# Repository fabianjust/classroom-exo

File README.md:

# classroom-exo
Classroom-ready open-source educational exoskeleton for biomedical and control engineering

The classroom Exo development is guided by the manual.
The manual is designed to assist you in seamlessly transitioning from EduExoPro to Classroom Exo. Whether you're a developer, educator, or enthusiast, the detailed content in each folder aims to provide clarity and guidance.

How to Use This Manual:
Begin by reading through the manual to familiarize yourself with the upgrade process.
Depending on your area of interest or expertise, navigate to the specific folders that match your requirements—whether it's CAD, PCB design, electronics, or material lists.
Feel free to collaborate by providing feedback, raising issues, or contributing to the ongoing development of Classroom Exo. Your input is highly valued.

We prepared three lab instructions for a) Force Control, b) Muscle Activity Control, and c) PID Control for Biomedical and Control Engineering University Education. Feel free to use these documents to build your own lab for a physical human-machine interaction, health robotics, and for all control theory courses.

If you want to know more about the Classroom Exo, check out the corresponding Journal Paper: https://www.degruyter.com/document/doi/10.1515/auto-2023-0208/html

We hope this manual serves as a valuable resource in your journey to implement Classroom Exo. 
Happy exploring and building with Classroom Exo!

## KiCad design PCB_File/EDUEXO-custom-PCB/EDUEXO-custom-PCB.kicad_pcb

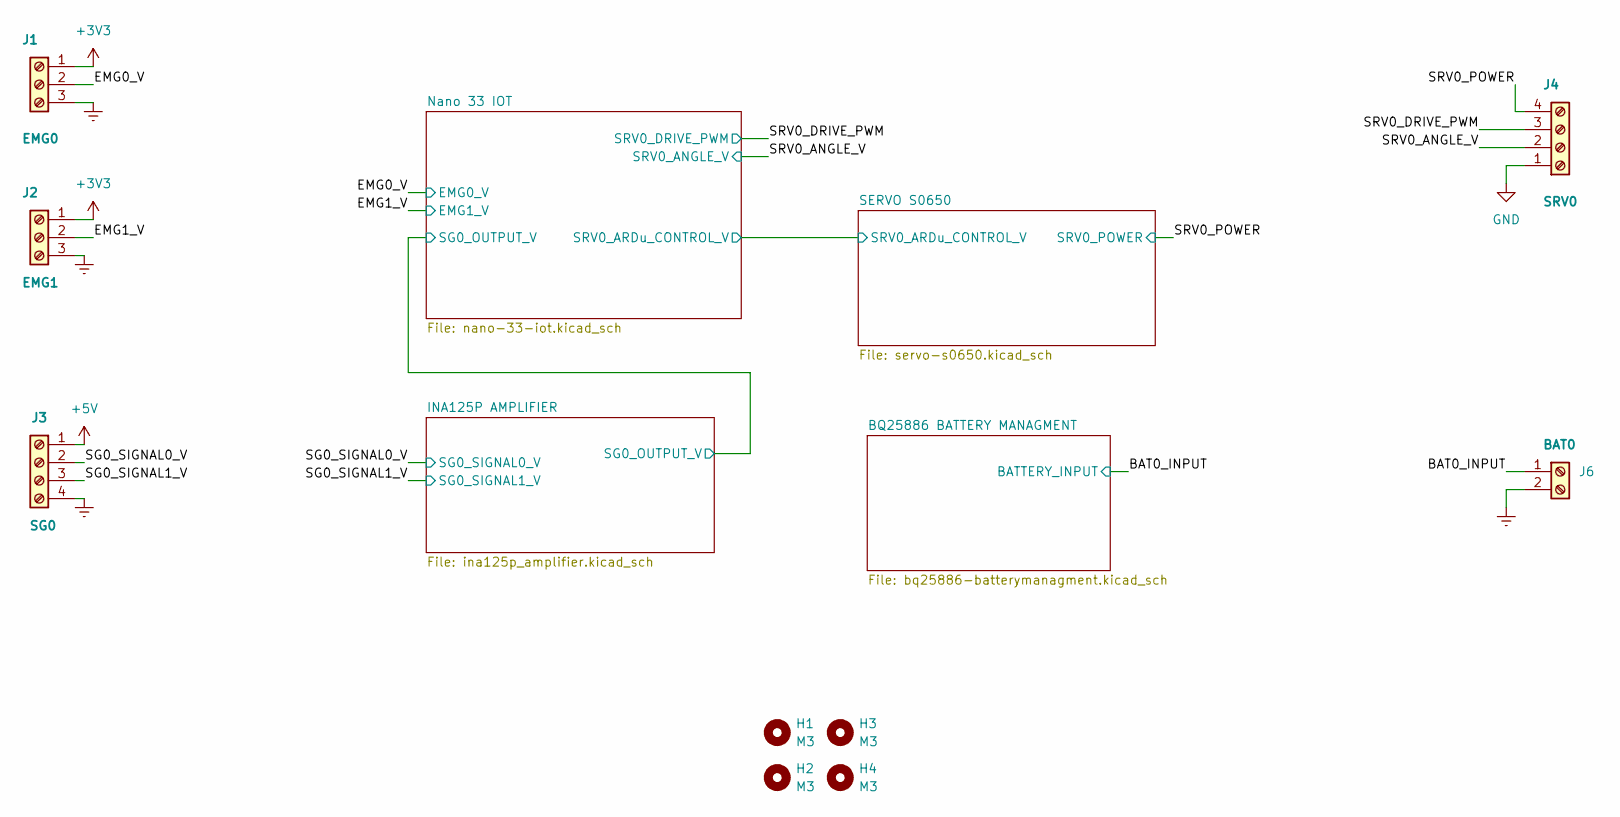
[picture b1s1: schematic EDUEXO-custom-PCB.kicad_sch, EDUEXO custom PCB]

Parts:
H1, H2, H3, H4: M3; MountingHole_3.2mm_M3
J1: EMG0; TE_1-2834011-3; MPN 1-2834011-3
J2: EMG1; TE_1-2834011-3; MPN 1-2834011-3
J3: SG0; TE_1-2834011-4; MPN 1-2834011-4
J4: SRV0; TE_1-2834011-4; MPN 1-2834011-4
J6: BAT0; TE_1-2834011-2; MPN 1-2834011-2

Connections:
+5V: J3.1; also elsewhere on the board
/BAT0_INPUT: J6.1; also elsewhere on the board
/EMG0_V: J1.2; also elsewhere on the board
/EMG1_V: J2.2; also elsewhere on the board
/SG0_SIGNAL0_V: J3.2; also elsewhere on the board
/SG0_SIGNAL1_V: J3.3; also elsewhere on the board
/SRV0_ANGLE_V: J4.2; also elsewhere on the board
/SRV0_DRIVE_PWM: J4.3; also elsewhere on the board
/SRV0_POWER: J4.4; also elsewhere on the board

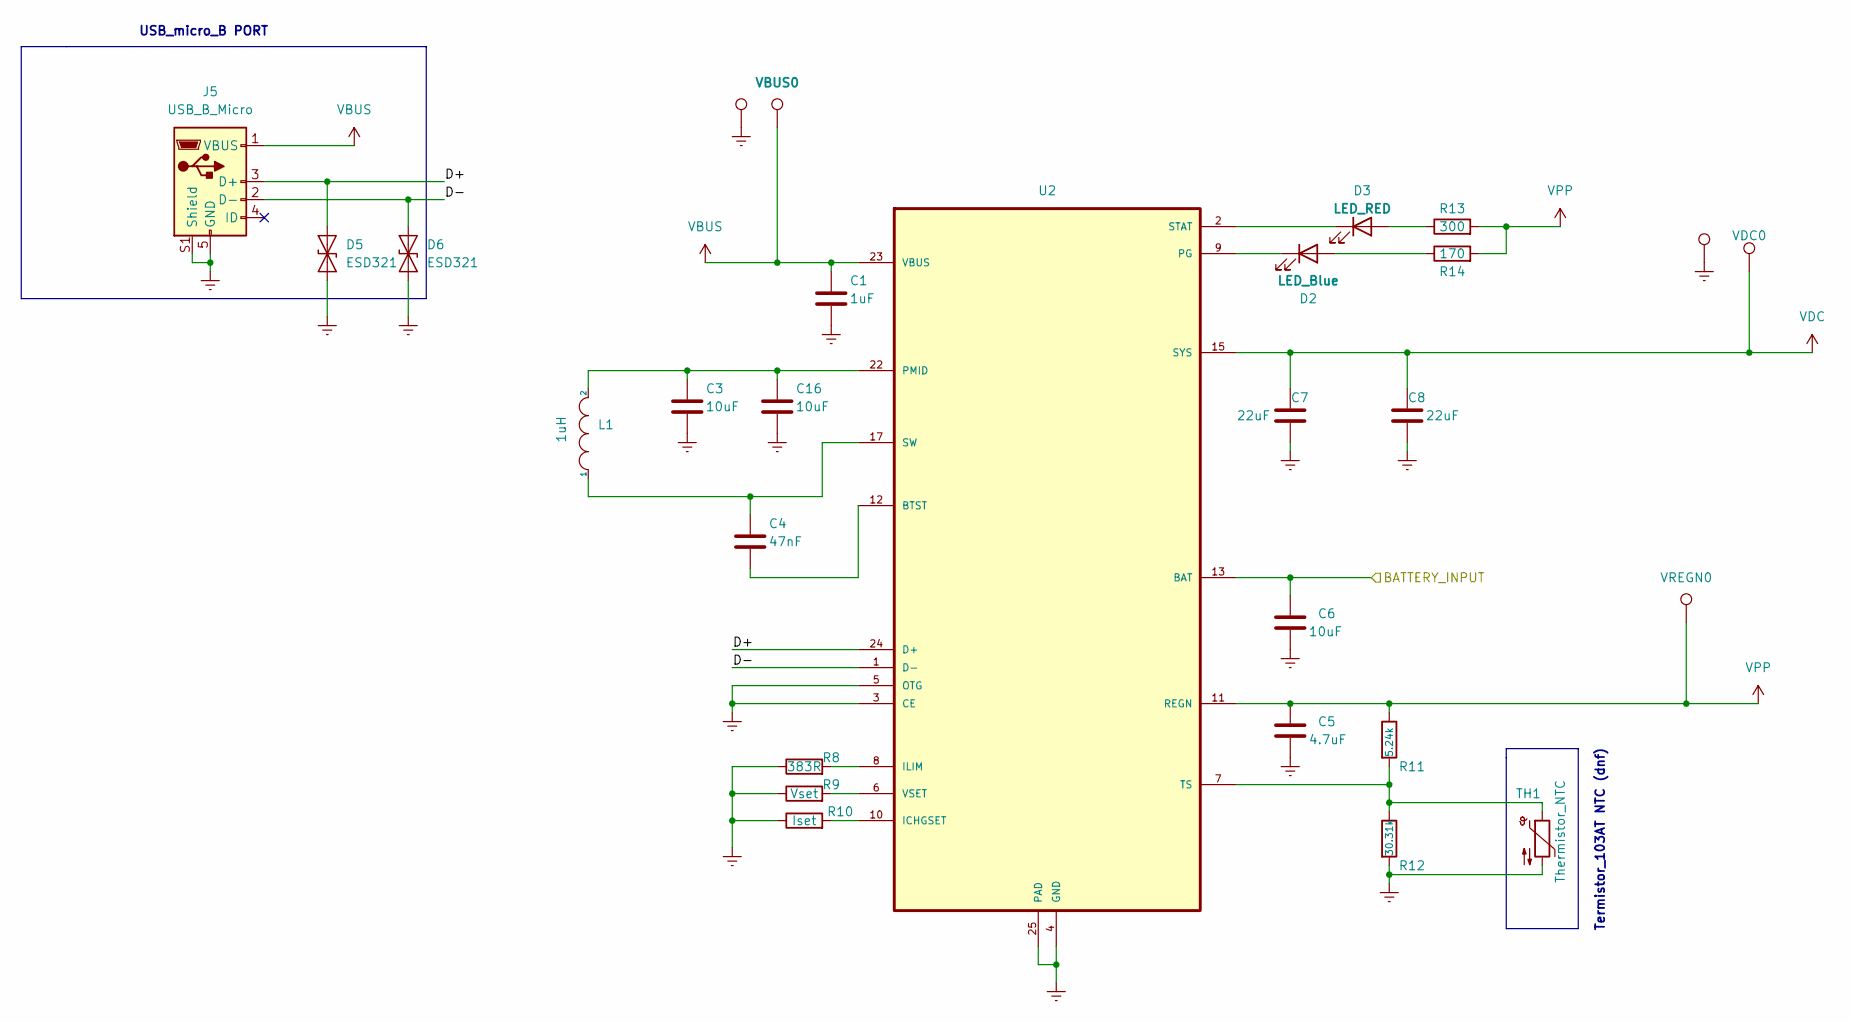
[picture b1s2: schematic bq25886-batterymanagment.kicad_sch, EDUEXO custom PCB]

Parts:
C1: 1uF; C_0805_2012Metric; MPN C2012X7R1H105K125AB
C3, C6, C16: 10uF; C_0805_2012Metric; MPN C2012X5R1E106K125AB
C4: 47nF; C_0805_2012Metric; MPN C2012X7T2W473K125AA
C5: 4.7uF; C_0805_2012Metric; MPN C2012X5R1E475K125AB
C7, C8: 22uF; C_0805_2012Metric; MPN C2012X5R1V226M125AC
D2: LED_Blue; LED_0603_1608Metric; MPN LTST-C191TBKT
D3: LED_RED; LED_0603_1608Metric; MPN LTST-C191KRKT
D5, D6: ESD321; D_0402_1005Metric; MPN ESD321DPYR
GND2, GND4: TestPoint; TestPoint_Keystone_5000-5004_Miniature; MPN 5002
J5: USB_B_Micro; USB_micro_B_10118192-0002LF; MPN 10118192-0002LF
L1: 1uH; L_0630CDMCCDS-1R5MC; MPN 0630CDMCCDS-1R5MC
R8: 383R; R_0805_2012Metric; MPN RC0805FR-07383RL
R9: Vset; R_0805_2012Metric
R10: Iset; R_0805_2012Metric
R11: 5.24k; R_0805_2012Metric; MPN RC0805FR-075K23L
R12: 30.31k; R_0805_2012Metric; MPN RC0805FR-0730K1L
R13: 300; R_0805_2012Metric; MPN RC0805JR-07300RL
R14: 170; R_0805_2012Metric; MPN RC0805FR-07174RL
TH1: Thermistor_NTC; R_0805_2012Metric
U2: BQ25886RGER; Texas_S-PVQFN-N24_EP2.1x2.1mm_ThermalVias; MPN BQ25886RGER
VBUS0: TestPoint; TestPoint_Keystone_5000-5004_Miniature; MPN 5002
VDC0: TestPoint; TestPoint_Keystone_5000-5004_Miniature; MPN 5002
VREGN0: TestPoint; TestPoint_Keystone_5000-5004_Miniature; MPN 5002

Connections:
/BAT0_INPUT: C6.1, U2.13 (BAT), U2.14 (BAT); also elsewhere on the board
/BQ25886 BATTERY MANAGMENT/D+: D5.2 (A2), J5.3 (D+), U2.24 (D+)
/BQ25886 BATTERY MANAGMENT/D-: D6.2 (A2), J5.2 (D-), U2.1 (D-)
unnamed: C4.1, L1.1, U2.17 (SW), U2.18 (SW)
unnamed: C4.2, U2.12 (BTST)
unnamed: C3.1, C16.1, L1.2, U2.21 (PMID), U2.22 (PMID)
unnamed: D2.1 (K), U2.9 (PG)
unnamed: D2.2 (A), R14.1
unnamed: D3.1 (K), U2.2 (STAT)
unnamed: D3.2 (A), R13.1
unnamed: R8.2, U2.8 (ILIM)
unnamed: R9.2, U2.6 (VSET)
unnamed: R10.2, U2.10 (ICHGSET)
unnamed: R11.2, R12.1, TH1.1, U2.7 (TS)
VBUS: C1.1, J5.1 (VBUS), U2.23 (VBUS), VBUS0.1
VDC: C7.1, C8.1, U2.15 (SYS), U2.16 (SYS), VDC0.1; also elsewhere on the board
VPP: C5.1, R11.1, R13.2, R14.2, U2.11 (REGN), VREGN0.1

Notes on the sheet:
USB_micro_B PORT
Termistor_103AT NTC (dnf)

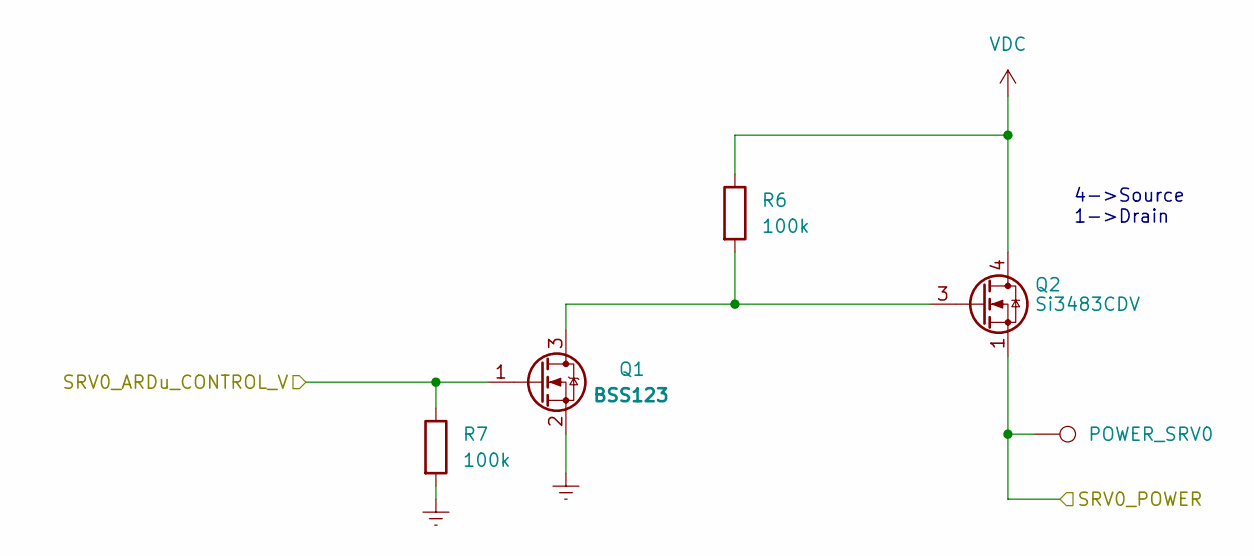
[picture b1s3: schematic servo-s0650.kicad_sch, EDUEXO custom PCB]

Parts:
POWER_SRV0: TestPoint; TestPoint_Keystone_5000-5004_Miniature; MPN 5002
Q1: BSS123; SOT-23; MPN BSS123
Q2: Si3483CDV; TSOT-23-6; MPN Si3483CDV
R6, R7: 100k; R_0805_2012Metric; MPN RC0805FR-13100KL

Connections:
/Nano 33 IOT /SRV0_ARDu_CONTROL_V: Q1.1 (G), R7.1; also elsewhere on the board
/SRV0_POWER: POWER_SRV0.1, Q2.1 (D), Q2.2 (D), Q2.5 (D), Q2.6 (D); also elsewhere on the board
unnamed: Q1.3 (D), Q2.3 (G), R6.2
VDC: Q2.4 (S), R6.1; also elsewhere on the board

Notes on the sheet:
4->Source 1->Drain

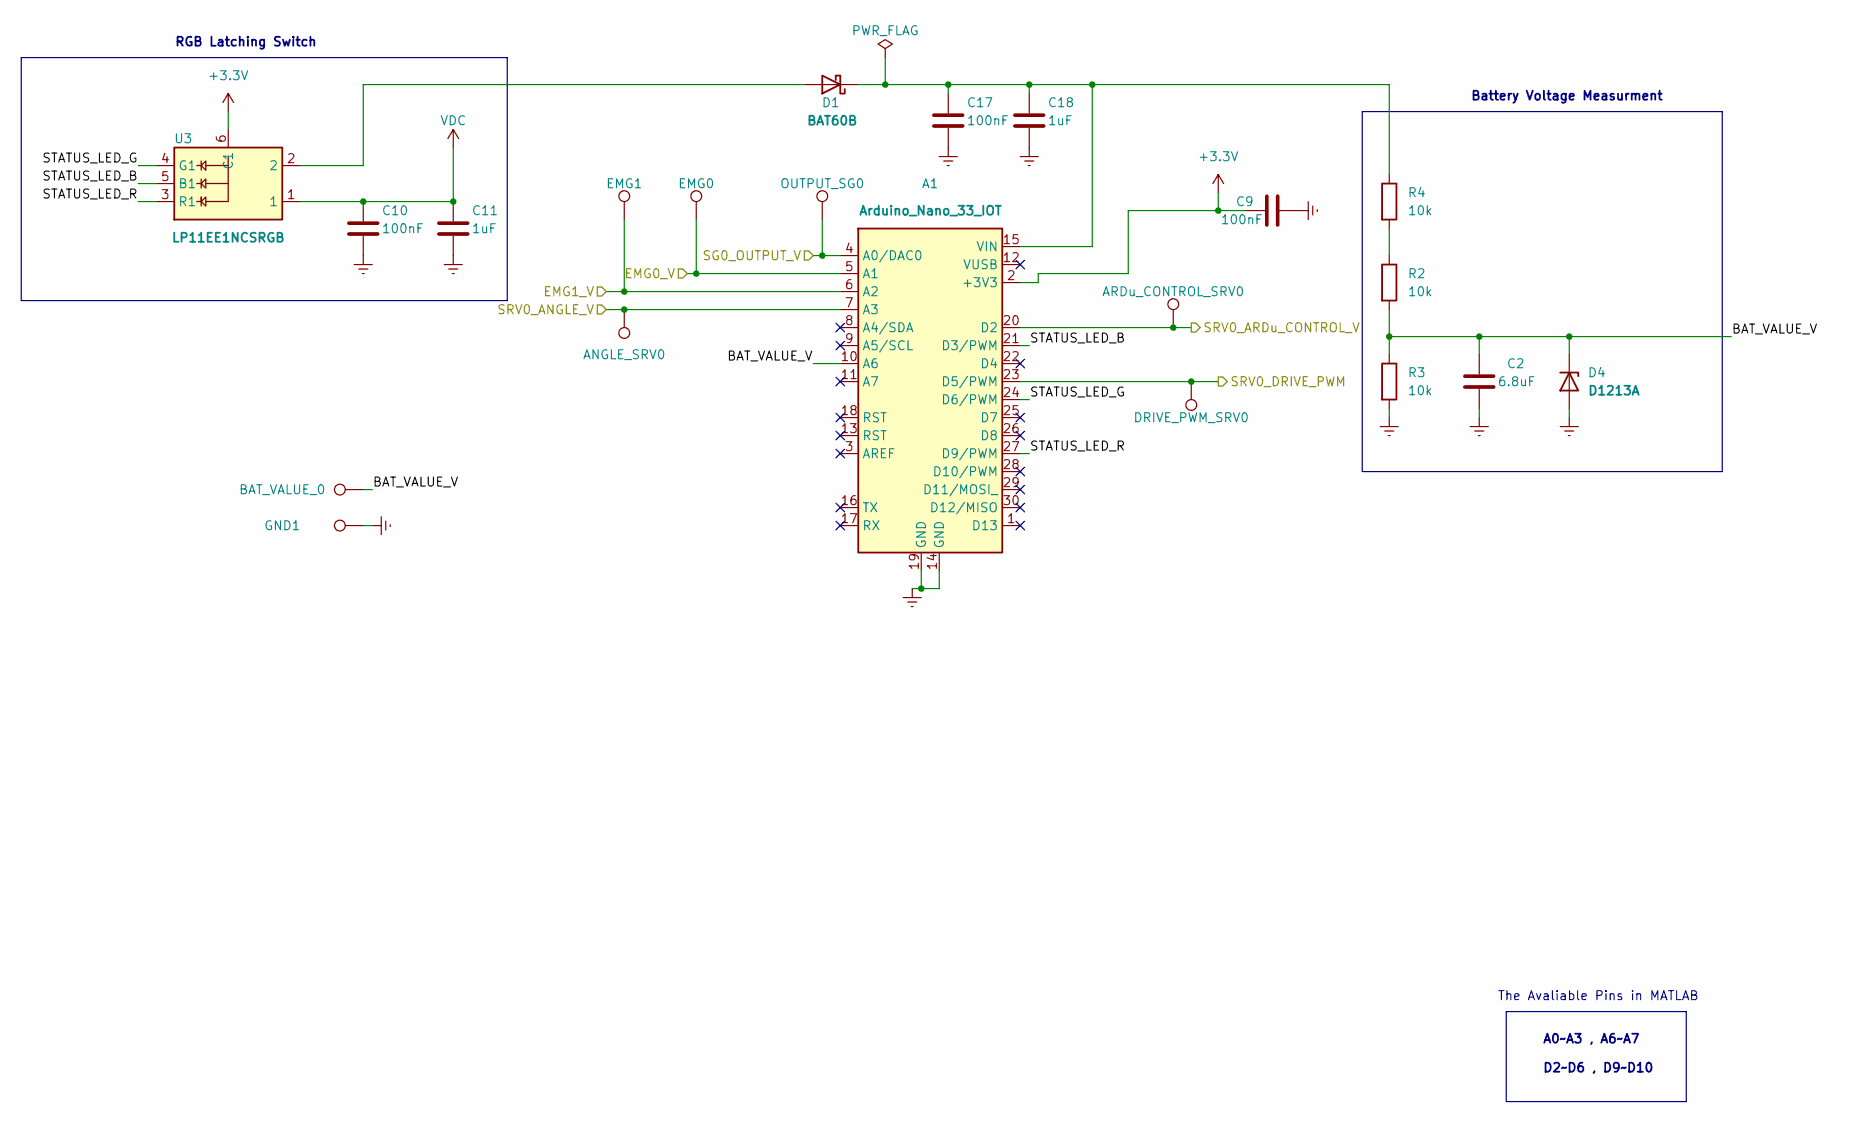
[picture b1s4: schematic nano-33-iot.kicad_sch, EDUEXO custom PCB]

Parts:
A1: Arduino_Nano_33_IOT; MODULE_ABX00027_ThroughHoles; MPN ABX00027
ANGLE_SRV0: TestPoint; TestPoint_Keystone_5000-5004_Miniature; MPN 5002
ARDu_CONTROL_SRV0: TestPoint; TestPoint_Keystone_5000-5004_Miniature; MPN 5002
BAT_VALUE_0: TestPoint; TestPoint_Keystone_5000-5004_Miniature; MPN 5002
C2: 6.8uF; C_0805_2012Metric; MPN C2012X8L0J685K125AC
C9, C10, C17: 100nF; C_0805_2012Metric; MPN C2012X7R2A104K125AA
C11, C18: 1uF; C_0805_2012Metric; MPN C2012X7R1H105K125AB
D1: BAT60B; D_SOD-323; MPN BAT60BE6327HTSA1
D4: D1213A; D_SOD-323; MPN D1213A-01WS-7
DRIVE_PWM_SRV0: TestPoint; TestPoint_Keystone_5000-5004_Miniature; MPN 5002
EMG0, EMG1: TestPoint; TestPoint_Keystone_5000-5004_Miniature; MPN 5002
GND1: TestPoint; TestPoint_Keystone_5000-5004_Miniature; MPN 5002
OUTPUT_SG0: TestPoint; TestPoint_Keystone_5000-5004_Miniature; MPN 5002
R2, R3, R4: 10k; R_0805_2012Metric; MPN RC0805JR-0710KL
U3: LP11EE1NCSRGB; SW_LP11EE1NCSRGB; MPN LP11EE1NCSRGB

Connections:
/EMG0_V: A1.5 (A1), EMG0.1; also elsewhere on the board
/EMG1_V: A1.6 (A2), EMG1.1; also elsewhere on the board
/INA125P AMPLIFIER/SG0_OUTPUT_V: A1.4 (A0/DAC0), OUTPUT_SG0.1; also elsewhere on the board
/Nano 33 IOT /BAT_VALUE_V: A1.10 (A6), BAT_VALUE_0.1, C2.1, D4.1 (K), R2.2, R3.1
/Nano 33 IOT /SRV0_ARDu_CONTROL_V: A1.20 (D2), ARDu_CONTROL_SRV0.1; also elsewhere on the board
/Nano 33 IOT /STATUS_LED_B: A1.21 (D3/PWM), U3.5 (B1)
/Nano 33 IOT /STATUS_LED_G: A1.24 (D6/PWM), U3.4 (G1)
/Nano 33 IOT /STATUS_LED_R: A1.27 (D9/PWM), U3.3 (R1)
/SRV0_ANGLE_V: A1.7 (A3), ANGLE_SRV0.1; also elsewhere on the board
/SRV0_DRIVE_PWM: A1.23 (D5/PWM), DRIVE_PWM_SRV0.1; also elsewhere on the board
unnamed: A1.15 (VIN), C17.1, C18.1, D1.1 (K), R4.1
unnamed: D1.2 (A), U3.2
unnamed: R2.1, R4.2
VDC: C10.1, C11.1, U3.1; also elsewhere on the board

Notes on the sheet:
A0~A3 , A6~A7 D2~D6 , D9~D10
The Avaliable Pins in MATLAB
RGB Latching Switch
Battery Voltage Measurment

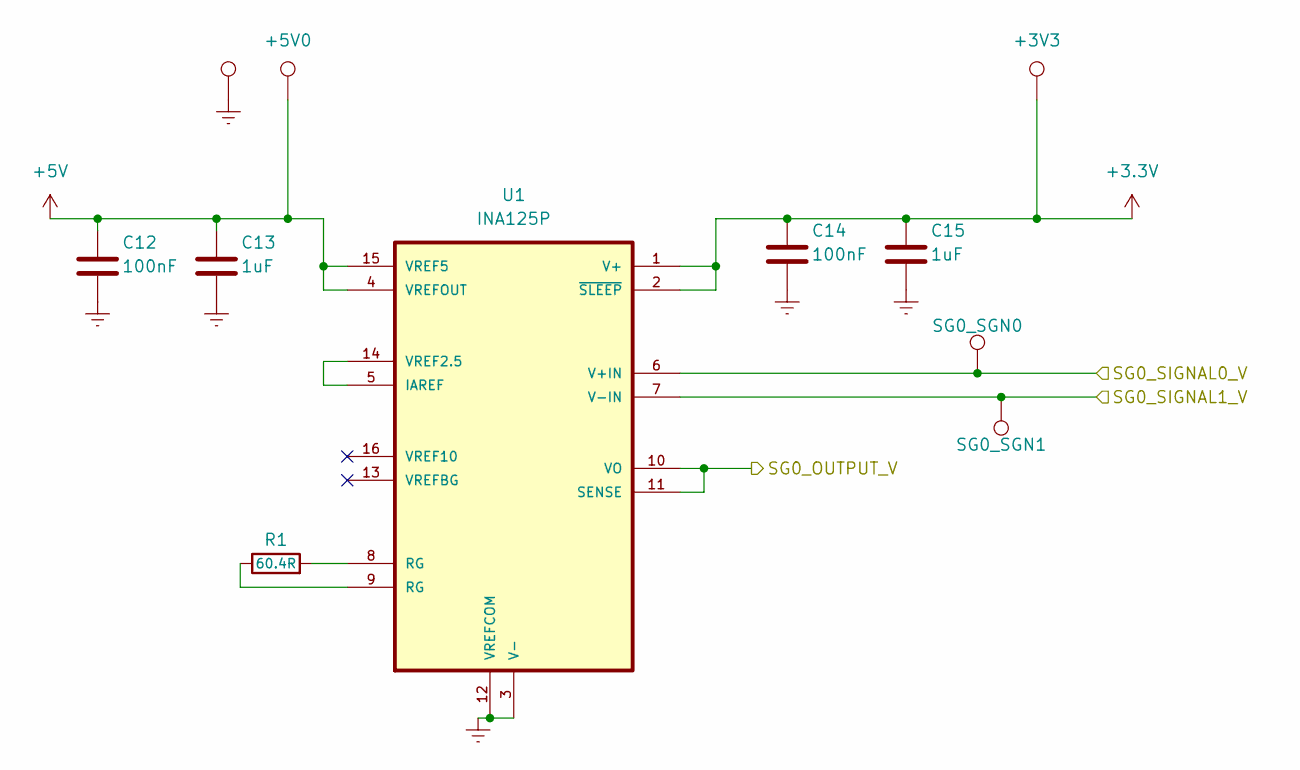
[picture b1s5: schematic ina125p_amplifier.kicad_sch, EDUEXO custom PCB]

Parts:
+3V3, +5V0: TestPoint; TestPoint_Keystone_5000-5004_Miniature; MPN 5002
C12, C14: 100nF; C_0805_2012Metric; MPN C2012X7R2A104K125AA
C13, C15: 1uF; C_0805_2012Metric; MPN C2012X7R1H105K125AB
GND3: TestPoint; TestPoint_Keystone_5000-5004_Miniature; MPN 5002
R1: 60.4R; R_0805_2012Metric; MPN RC0805FR-0760R4L
SG0_SGN0, SG0_SGN1: TestPoint; TestPoint_Keystone_5000-5004_Miniature; MPN 5002
U1: INA125P; DIP794W45P254L1969H508Q16; MPN INA125P

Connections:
+5V: +5V0.1, C12.1, C13.1, U1.4 (VREFOUT), U1.15 (VREF5); also elsewhere on the board
/INA125P AMPLIFIER/SG0_OUTPUT_V: U1.10 (VO), U1.11 (SENSE); also elsewhere on the board
/SG0_SIGNAL0_V: SG0_SGN0.1, U1.6 (V+IN); also elsewhere on the board
/SG0_SIGNAL1_V: SG0_SGN1.1, U1.7 (V-IN); also elsewhere on the board
unnamed: R1.1, U1.9 (RG)
unnamed: R1.2, U1.8 (RG)
unnamed: U1.5 (IAREF), U1.14 (VREF2.5)

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
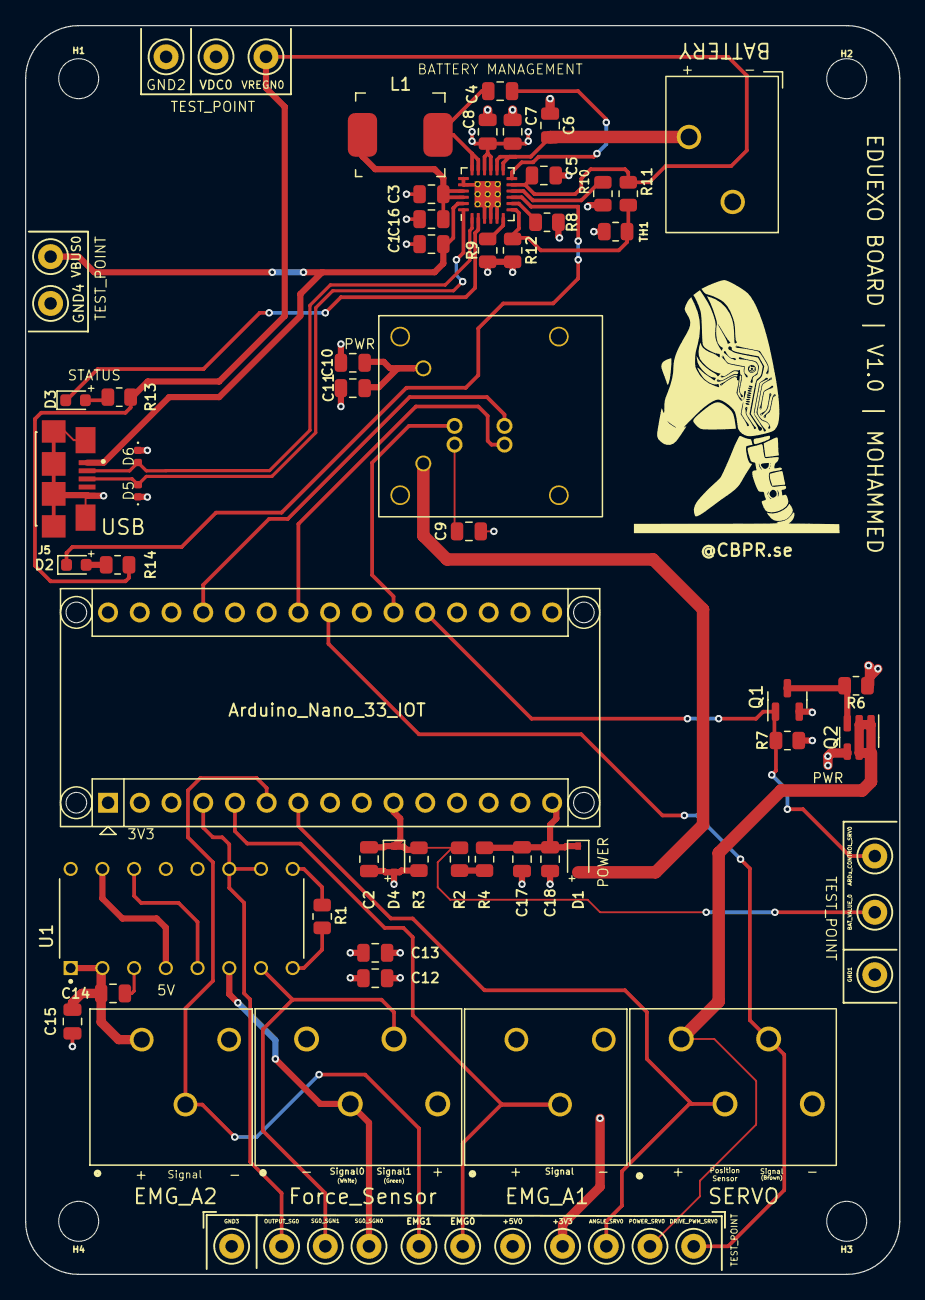
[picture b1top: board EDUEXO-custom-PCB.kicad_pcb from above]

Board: 4 copper layers, 70.0 x 100.0 mm, 74 parts (0 on the bottom side), 40 nets.

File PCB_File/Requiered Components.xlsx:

Reference | Value | MPN | Qty/unit | LINK | Column1
> R2-R4 | 10k | RC0805JR-0710KL | 3 | LINK
R13 | 300R | RC0805JR-07300RL | 1 | LINK
R1 | 60.4R | RC0805FR-0760R4L | 1 | LINK
R11 | 5.24k | RC0805FR-075K23L | 1 | LINK
R12 | 30.31k | RC0805FR-0730K1L | 1 | LINK
> R6, R7 | 100k | RC0805FR-13100KL | 2 | LINK
R8 | 383R | RC0805FR-07383RL | 1 | LINK
R14 | 170R | RC0805FR-07174RL | 1 | LINK
D3 | LED_RED | LTST-C191KRKT | 1 | LINK
D2 | LED_Blue | LTST-C191TBKT | 1 | LINK
> D5, D6 | ESD321 | ESD321DPYR | 2 | LINK
D4 | D1213A | D1213A-01WS-7 | 1 | LINK
C2 | 6.8uF | C2012X8L0J685K125AC | 1 | LINK
C4 | 47nF | C2012X7T2W473K125AA | 1 | LINK
> C9, C10, C12, C14, C17 | 100nF | C2012X7R2A104K125AA | 5 | LINK
> C1, C11, C13, C15, C18 | 1uF | C2012X7R1H105K125AB | 5 | LINK
> C7, C8 | 22uF | C2012X5R1V226M125AC | 2 | LINK
C5 | 4.7uF | C2012X5R1E475K125AB | 1 | LINK
> C3, C6, C16 | 10uF | C2012X5R1E106K125AB | 3 | LINK
D1 | BAT60B | BAT60BE6327HTSA1 | 1 | LINK
J5 | USB_B_Micro | 10118192-0002LF | 1 | LINK
J4 | SRV0 | 1-2834011-4 | 1 | LINK
J3 | SG0 | 1-2834011-4 | 1 | LINK
J2 | EMG1 | 1-2834011-3 | 1 | LINK
J1 | EMG0 | 1-2834011-3 | 1 | LINK
J6 | BAT0 | 1-2834011-2 | 1 | LINK
L1 | 1uH | 0630CDMCCDS-1R5MC | 1 | LINK
U3 (RGBSwitch) | LP11EE1NCSRGB | LP11EE1NCSRGB | 1 | LINK
U2 (BatteryManagment) | BQ25886RGER | BQ25886RGER | 1 | LINK
U1 (Amplifier) | INA125P | INA125P | 3 | LINK
U1 (Socket) | INA125P | ICM-316-1-GT-HT | 3 | LINK
R10 | Iset (5.7k) | RC0805FR-075K76L | 1 | LINK
R9 | Vset(150k) | RC0805FR-07150KL | 1 | LINK
Q2 | Si3483CDV | SI3483CDV-T1-GE3 | 1 | LINK
Q1 | BSS123 | BSS123 | 1 | LINK
A1 | Arduino_Nano_33_IOT | PPPC101LFBN-RC (10P) | 2 | LINK
A1 | Arduino_Nano_33_IOT | PPPC051LFBN-RC (5P) | 2 | LINK
PWR_TP | TestPoint (White) | 5000 | 6 | LINK
SRV0_TP | TestPoint (Yellow) | 5004 | 4 | LINK
> EMG0, EMG1_TP | TestPoint (Orange) | 5003 | 2 | LINK
> GND_TP | TestPoint (Black) | 5001 | 4 | LINK
SG0_TP | TestPoint (White) | 5002 | 3 | LINK
Myoware Cable | Myoware Cable | CAB-12970 | 2 | LINK
Myoware Cable Shield | Myoware Cable Shield | Myoware Cable Shield | 2 | LINK
Screw thread Insert M3 |  | K0978.03 | 15 | Link
Screw thread Insert M4 |  | K0978.04 | 15 | link
Screw M3 |  | S3-6-P | 15 | Link
Screw M4 |  | S4-45-P | 15 | link
Battery | 7.4V/8.4V | CL-LP503759-2S1P |  | Link
Soldering | NC191LT10 | NC191LT10
SRA NO CLEAN PASTE FLUX | FLS135NC | FLS135NC
 |  |  |  |  |  | # The quantities provided in this list represent the minimum requirement. We st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

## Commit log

2023-11-08 CAD for Github LRS
2023-11-08 PCB GUI and force/EMG control
2023-11-30 Delete 1_CAD_File/Shoulder 0.6 nozzle.stl
    Not needed
2023-11-30 Delete 1_CAD_File/Shoulder_Upper-part.stl
    Not needed
2023-12-09 Open-Source Material for Scientific Paper
2023-12-09 Manual for the Repository
2024-02-01 Upload PI Optimal L2 stability GUI
2024-10-14 Classroom Exo Arduino Code
2024-10-14 Updated Matlab GUI
2024-10-14 Delete Updated BT-GUI_10-24/DataManagementFunctions.m
    deleted
2024-10-14 Delete Updated BT-GUI_10-24/ControlFunctions.m
    deleted
2024-10-14 updated gitignore
2024-10-14 Delete Updated BT-GUI_10-24/BT_Calibration_GUI.mlapp
    deleted
2024-10-14 fixed Pin select
2025-01-20 Commit Changes Nov 2024
2025-01-20 Supplementary Materials
2025-01-20 Update Manuel Delete
    Old Manual Delete
2025-01-20 Adapt
2025-01-20 Manual
    Manual
2025-01-29 Lab Instructions: EMG Force Control PID Control
    Lab Instructions: EMG Force Control PID Control
